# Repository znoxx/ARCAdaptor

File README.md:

ARCAdaptor
==========
https://github.com/znoxx/ARCAdaptor

Arcadaptor stuff - schematic, firmware, libs

For details, check http://adaptor.su
=======

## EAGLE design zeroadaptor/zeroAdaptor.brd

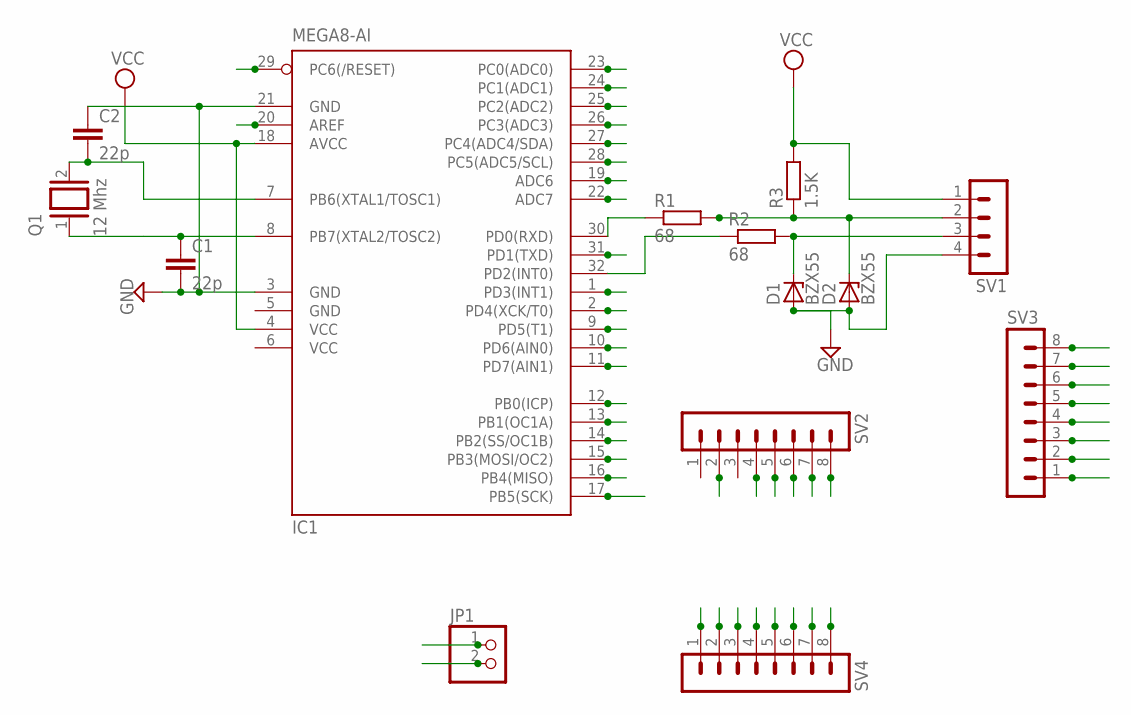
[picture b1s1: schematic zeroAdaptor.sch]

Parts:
C1, C2: 22p; C025-024X044
D1, D2: BZX55; DO35Z10
IC1: MEGA8-AI; TQFP32-08
JP1: PINHD-1X2; 1X02
Q1: 12 Mhz; QS
R1, R2: 68; 0204/7
R3: 1.5K; 0204/7
SV1: MA04-1
SV2, SV3, SV4: MA08-1

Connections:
ADC6: IC1.19 (ADC6), SV3.3
ADC7: IC1.22 (ADC7), SV3.6
AREF: IC1.20 (AREF), SV3.4
GND: C1.2, C2.1, D1.A, D2.A, IC1.3 (GND), IC1.5 (GND), IC1.21 (GND), SV1.4, SV3.5
unnamed: C2.2, IC1.7 (PB6(XTAL1/TOSC1)), Q1.2
unnamed: C1.1, IC1.8 (PB7(XTAL2/TOSC2)), Q1.1
unnamed: IC1.30 (PD0(RXD)), R1.1
unnamed: IC1.32 (PD2(INT0)), R2.1
unnamed: D1.C, R2.2, SV1.3
unnamed: D2.C, R1.2, R3.1, SV1.2
PB0: IC1.12 (PB0(ICP)), SV4.4
PB1: IC1.13 (PB1(OC1A)), SV4.5
PB2: IC1.14 (PB2(SS/OC1B)), SV4.6
PB3: IC1.15 (PB3(MOSI/OC2)), SV4.7
PB4: IC1.16 (PB4(MISO)), SV4.8
PB5: IC1.17 (PB5(SCK)), SV3.1
PC0: IC1.23 (PC0(ADC0)), SV3.7
PC1: IC1.24 (PC1(ADC1)), SV3.8
PC2: IC1.25 (PC2(ADC2)), SV2.8
PC3: IC1.26 (PC3(ADC3)), SV2.7
PC4: IC1.27 (PC4(ADC4/SDA)), SV2.6
PC5: IC1.28 (PC5(ADC5/SCL)), SV2.5
PC6: IC1.29 (PC6(/RESET)), SV2.4
PD1: IC1.31 (PD1(TXD)), SV2.2
PD3: IC1.1 (PD3(INT1)), JP1.1
PD4: IC1.2 (PD4(XCK/T0)), JP1.2
PD5: IC1.9 (PD5(T1)), SV4.1
PD6: IC1.10 (PD6(AIN0)), SV4.2
PD7: IC1.11 (PD7(AIN1)), SV4.3
VCC: IC1.4 (VCC), IC1.6 (VCC), IC1.18 (AVCC), R3.2, SV1.1, SV3.2

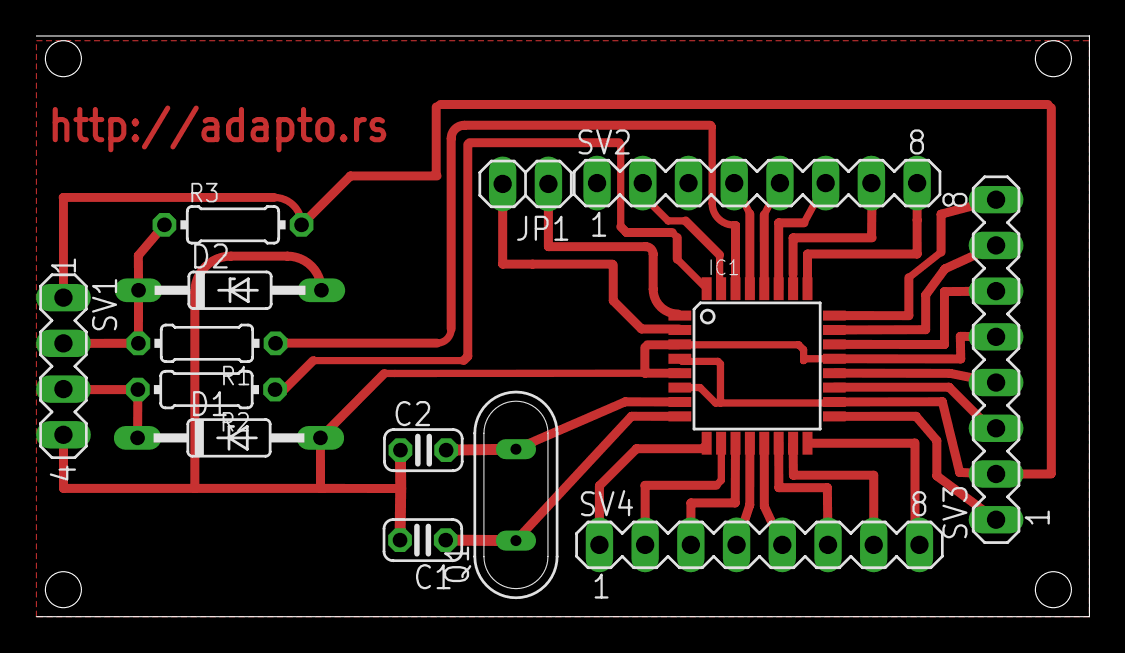
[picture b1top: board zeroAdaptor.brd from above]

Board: 2 copper layers, 58.5 x 32.3 mm, 14 parts (0 on the bottom side), 30 nets.

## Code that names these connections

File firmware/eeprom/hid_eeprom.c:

#include <avr/eeprom.h> 
#include "hid_keycodes.h"
#include "hid_input_mapping.h"

#if defined __AVR_ATmega8__
// Atmega8 Shift switch on
unsigned char EEMEM  eepShiftMapping[NUMBER_OF_INPUTS]=
{                       //  Pin Atmega  Function     XPIN
    AC_VolumeDown,      //  14  PB0     JOY2LEFT     X2S5
    KM_SHIFT_F7,        //  15  PB1     JOY2BUTTON2  X2S11
    KM_ALT_F4,          //  16  PB2     JOY2BUTTON3  X2S13
    AC_Mute,            //  17  PB3     JOY2START    X2S15
    KEY_DownArrow,      //  18  PB4     JOY1DOWN     X1S3
    KEY_UpArrow,        //  24  PC1     JOY1UP       X1S7
    KEY_LeftArrow,      //  23  PC0     JOY1LEFT     X1S5
    KEY_RightArrow,     //  17  PB5     JOY1RIGHT    X1S1
    KEY_Enter,          //  25  PC2     JOY1BUTTON1  X1S9
    KEY_Esc,            //  26  PC3     JOY1BUTTON2  X1S11
    KEY_Tab,            //  27  PC4     JOY1BUTTON3  X1S13
    KEY_P,              //  28  PC5     JOY1START    X1S15
    0,                  //   3  PD1     SHIFTSWITCH  shift X3S3
    KEY_5,              //   5  PD3     COINTRIGGER  X3S1
    KEY_PageDown,       //   6  PD4     JOY2DOWN     X2S3
    KEY_F7,             //  11  PD5     JOY2BUTTON1  X2S9
    AC_VolumeUp,        //  12  PD6     JOY2RIGHT    X2S7
    KEY_PageUp          //  13  PD7     JOY2UP       X2S1
};

// Atmega8 Shift switch off
unsigned char EEMEM eepNormalMapping[NUMBER_OF_INPUTS] =
{                       //  Pin Atmega  Function       XPIN
    J2_Left,            //  14  PB0     JOY2LEFT       X2N5
    J2_Button2,         //  15  PB1     JOY2BUTTON2    X2N11
    J2_Button3,         //  16  PB2     JOY2BUTTON3    X2N13
    KEY_2,              //  17  PB3     JOY2START      X2N15
    J1_Down,            //  18  PB4     JOY1DOWN       X1N3
    J1_Up,              //  24  PC1     JOY1UP         X1N7
    J1_Left,            //  23  PC0     JOY1LEFT       X1N5
    J1_Right,           //  17  PB5     JOY1RIGHT      X1N1
    J1_Button1,         //  25  PC2     JOY1BUTTON1    X1N9
    J1_Button2,         //  26  PC3     JOY1BUTTON2    X1N11
    J1_Button3,         //  27  PC4     JOY1BUTTON3    X1N13
    KEY_1,              //  28  PC5     JOY1START      X1N15
    0,                  //   3  PD1     SHIFTSWITCH    shift X3N3
    KEY_5,              //   5  PD3     COINTRIGGER    X3N1
    J2_Down,            //   6  PD4     JOY2DOWN       X2N3
    J2_Button1,         //  11  PD5     JOY2BUTTON1    X2N9
    J2_Right,           //  12  PD6     JOY2RIGHT      X2N7
    J2_Up               //  13  PD7     JOY2UP         X2N1
};

#elif defined __AVR_ATmega32__
// Atmega32 Shift switch on
unsigned char EEMEM eepShiftMapping[NUMBER_OF_INPUTS]=
{                       //  Pin Atmega  Board   Function
    KEY_5,              //  40  PA0     X6-1    COINTRIGGER
    0,                  //  39  PA1     X4-8    none
    0,                  //  38  PA2     X4-7    none
    AC_Mute,            //  37  PA3     X4-6    JOY2START
    KEY_P,              //  36  PA4     X4-5    JOY1START
    0,                  //  35  PA5     X4-4    JOY1BUTTON8
    0,                  //  34  PA6     X4-3    JOY1BUTTON7
    0,                  //  33  PA7     X4-2    JOY1BUTTON6
    0,                  //   1  PB0     X9-2    SHIFTSWITCH
    0,                  //   2  PB1     X7-1    JOY2BUTTON8
    0,                  //   3  PB2     X7-2    JOY2BUTTON7
    0,                  //   4  PB3     X8-1    JOY2BUTTON6
    0,                  //   5  PB4     X8-2    JOY2BUTTON5
    0,                  //   6  PB5     X5-1    JOY2BUTTON4
    KM_ALT_F4,          //   7  PB6     X5-2    JOY2BUTTON3
    KM_SHIFT_F7,        //   8  PB7     X5-3    JOY2BUTTON2
    KEY_UpArrow,        //  22  PC0     X3-2    JOY1UP
    KEY_LeftArrow,      //  23  PC1     X3-3    JOY1LEFT
    KEY_RightArrow,     //  24  PC2     X3-4    JOY1RIGHT
    KEY_Enter,          //  25  PC3     X3-5    JOY1BUTTON1
    KEY_Esc,            //  26  PC4     X3-6    JOY1BUTTON2
    KEY_Tab,            //  27  PC5     X3-7    JOY1BUTTON3
    0,                  //  28  PC6     X3-8    JOY1BUTTON4
    0,                  //  29  PC7     X4-1    JOY1BUTTON5
    KEY_F7,             //  15  PD1     X5-4    JOY2BUTTON1
    AC_VolumeUp,        //  17  PD3     X5-5    JOY2RIGHT
    AC_VolumeDown,      //  18  PD4     X5-6    JOY2LEFT
    KEY_PageUp,         //  19  PD5     X5-7    JOY2UP
    KEY_PageDown,       //  20  PD6     X5-8    JOY2DOWN
    KEY_DownArrow       //  21  PD7     X3-1    JOY1DOWN
};

// Atmega32 Shift switch on
unsigned char EEMEM eepShiftMapping[NUMBER_OF_INPUTS]=
{                       //  Pin Atmega  Board   Function
    KEY_5,              //  40  PA0     X6-1    COINTRIGGER
    0,                  //  39  PA1     X4-8    none
    0,                  //  38  PA2     X4-7    none
    AC_Mute,            //  37  PA3     X4-6    JOY2START
    KEY_P,              //  36  PA4     X4-5    JOY1START
    0,                  //  35  PA5     X4-4    JOY1BUTTON8
    0,                  //  34  PA6     X4-3    JOY1BUTTON7
    0,                  //  33  PA7     X4-2    JOY1BUTTON6
    0,                  //   1  PB0     X9-2    SHIFTSWITCH
    0,                  //   2  PB1     X7-1    JOY2BUTTON8
    0,                  //   3  PB2     X7-2    JOY2BUTTON7
    0,                  //   4  PB3     X8-1    JOY2BUTTON6
    0,                  //   5  PB4     X8-2    JOY2BUTTON5
    0,                  //   6  PB5     X5-1    JOY2BUTTON4
    KM_ALT_F4,          //   7  PB6     X5-2    JOY2BUTTON3
    KM_SHIFT_F7,        //   8  PB7     X5-3    JOY2BUTTON2
    KEY_UpArrow,        //  22  PC0     X3-2    JOY1UP
    KEY_LeftArrow,      //  23  PC1     X3-3    JOY1LEFT
    KEY_RightArrow,     //  24  PC2     X3-4    JOY1RIGHT
    KEY_Enter,          //  25  PC3     X3-5    JOY1BUTTON1
    KEY_Esc,            //  26  PC4     X3-6    JOY1BUTTON2
    KEY_Tab,            //  27  PC5     X3-7    JOY1BUTTON3
    0,                  //  28  PC6     X3-8    JOY1BUTTON4
    0,                  //  29  PC7     X4-1    JOY1BUTTON5
    KEY_F7,             //  15  PD1     X5-4    JOY2BUTTON1
    AC_VolumeUp,        //  17  PD3     X5-5    JOY2RIGHT
    AC_VolumeDown,      //  18  PD4     X5-6    JOY2LEFT
    KEY_PageUp,         //  19  PD5     X5-7    JOY2UP
    KEY_PageDown,       //  20  PD6     X5-8    JOY2DOWN
    KEY_DownArrow       //  21  PD7     X3-1    JOY1DOWN
};

#endif  // defined __AVR_ATmega8/32__

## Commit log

2013-11-30 Added schematic
    Initial version of ARCAdaptor schematic
2013-11-30 ARCAdaptor schematics
    ARCAdaptor schematics, initial verison
2013-11-30 Firmware, bootloader, arduino settings and some projects
    Added source code, bootloader, arduino settins and some projects to
    illustrate
2013-11-30 ATARIUSB patch
    Patch to make ARCAdaptor work with ATARIUSB by raphnet
2013-11-30 Added readme.txt for schematics, main readme updated
2013-11-30 Merge branch 'master' of https://github.com/znoxx/ARCAdaptor
    Conflicts:
    README.md
2013-11-30 .md update
2013-12-17 Stuff added, including V-USB arduino libs
    Added Arduino libs, Windows flash scripts, and win version of AVRDude.
2014-02-03 V-USB Keyboard library mod and sketch for Arduino
    Added new method to V-USB library : sendBuffer
    Added sketch to control ZX-Spectrum original 40 key keyboard
2014-02-03 Added initial ARCAdaptor arduino library
    ARCAdaptor pins for Arduino mapping
    just include “ARCAdaptor.h” to your sketch and start using ARCAdaptor
    pins in natural way
2014-02-04 readme.txt update
2014-02-10 Added patch to support HIDSerial component
    HIDSerial allows to debug via USB HID device, instead of serial.
    Original code:
    https://rayshobby.net/?p=7363
    https://github.com/rayshobby/hid-serial
2014-03-03 Added original 4nes4snes
    Original package 4nes4snes added
2014-03-03 Added original usbjoy compilation
    Added original usbjoy compilation - to keep consistent
2014-06-02 USBasp adaptation added
    Added project to use ARCAdaptor as USBasp programmer
2014-06-02 dir name update
2014-06-02 Added firmware hex
2015-04-03 Updated settings for Arduino 1.5.x
    Added arduino 1.5.x settings, previous moved to pre-1.5
2016-02-27 Added DYI version
    ZeroAdaptor - minimal version for PCB etching@home
2016-04-06 added images for WiKi migration
    Added folder for Wiki migration
2016-04-06 added title image
    Title image added
2016-04-07 Online eeprom editor published
    Online eeprom editor published, finally.
    Resolved some dependency issues, now ready to be used stand-alone.
2016-04-08 Markdown version published
    Markdown source code and Makefile for panic
2016-05-17 Fixed flash scripts, added linux version
2016-10-21 Initial working version
2016-10-21 Moar images
2017-05-08 legacy version rename
2017-05-08 Added Node.JS version of online editor
2017-07-13 Aligned with Heroku
2017-10-13 Added ATX driver example pic
2017-10-13 Image optimization
2020-05-11 Adopted original I2C-Tiny-USB from Till Harbaum
2020-05-11 Bump morgan from 1.8.2 to 1.10.0 in /online-editor
    Bumps [morgan](https://github.com/expressjs/morgan) from 1.8.2 to 1.10.0.
    - [Release notes](https://github.com/expressjs/morgan/releases)
    - [Changelog](https://github.com/expressjs/morgan/blob/master/HISTORY.md)
    - [Commits](https://github.com/expressjs/morgan/compare/1.8.2...1.10.0)
2023-04-16 Uplifting version to 1.3.1, moving to docker
2023-04-16 Nginx example updated to real one
